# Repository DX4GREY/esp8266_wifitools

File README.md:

# WiFi Tools (esp8266)

Scan for WiFi devices, block selected connections, Start EvilTwin with custom html, create dozens of networks and confuse WiFi scanners.

## Password

The password for `A F` is `Dx4White`

## About this Project

This firmware allows you to easily perform a variety of actions to test 802.11 networks using an [ESP8266](https://www.espressif.com/en/products/socs/esp8266). It's also a great project for learning about WiFi, microcontrollers, Arduino, hacking and electronics/programming in general.  

The deauthentication attack is the main feature, which can be used to disconnect devices from their WiFi network.  
Although this denial-of-service attack is nothing new, a lot of devices are still vulnerable to it. Luckily this is slowly changing with more WiFi 6 enabled devices being used. But a lot of outdated WiFi devices remain in place, for example in cheap IoT hardware.
With an ESP8266 Deauther, you can easily test this attack on your 2.4GHz WiFi network/devices and see whether it's successful or not. And if it is, you know you should upgrade your network.

## Disclaimer

This project is a proof of concept for testing and educational purposes.  
Neither the ESP8266, nor its SDK was meant or built for such purposes. **Bugs can occur!**  

**Use it only against your own networks and devices!**  
Please check the legal regulations in your country before using it.  
We don't take any responsibility for what you do with this program.

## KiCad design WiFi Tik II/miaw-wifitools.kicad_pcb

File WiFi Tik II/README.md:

# WiFiTik Prototype
This project used base firmware [WiFi Tools](https://github.com/dx4grey/esp8266_wifitools)

## Component quantity

| Designator     | Quantity | Value                             | Pack                                | MPN                                | Mount Type |
| -------------- | -------- | --------------------------------- | ----------------------------------- | ---------------------------------- | ---------- |
| 1              | 1        | OLED                              |                                     |                                    | THT        |
| D1 MINI        | 1        | Wemos-D1-mini                     | wemos-d1-mini-connectors-only       |                                    | THT        |
| A, B, DOWN, UP | 4        | SW_PUSH_6mm                       | SW_PUSH_6mm                         |                                    | THT        |
| Hole, Hole, Hole, Hole | 4 | MountingHole_2.1mm              | MountingHole_2.1mm                  |                                    | THT        |
| LED            | 1        | LED_Cree-XQ_HandSoldering         | LED_Cree-XQ_HandSoldering           |                                    | SMT        |
| R1, R2         | 2        | Resistor                          | Resistor                            |                                    | THT        |
| RX, TX         | 2        | Pin_D0.9mm_L10.0mm_W2.4mm_FlatFork | Pin_D0.9mm_L10.0mm_W2.4mm_FlatFork |                                    | THT        |
| VIN            | 1        | Power 5V                           | Power 5V                            |                                    | SMT        |

## PCB Previews

<details>
  <summary>Front View</summary>

</details>

<details>
  <summary>Back View</summary>

</details>

## About this Project

This firmware allows you to easily perform a variety of actions to test 802.11 networks using an [ESP8266](https://www.espressif.com/en/products/socs/esp8266). It's also a great project for learning about WiFi, microcontrollers, Arduino, hacking and electronics/programming in general.  

The deauthentication attack is the main feature, which can be used to disconnect devices from their WiFi network.  
Although this denial-of-service attack is nothing new, a lot of devices are still vulnerable to it. Luckily this is slowly changing with more WiFi 6 enabled devices being used. But a lot of outdated WiFi devices remain in place, for example in cheap IoT hardware.
With an ESP8266 Deauther, you can easily test this attack on your 2.4GHz WiFi network/devices and see whether it's successful or not. And if it is, you know you should upgrade your network.

## Disclaimer

This project is a proof of concept for testing and educational purposes.  
Neither the ESP8266, nor its SDK was meant or built for such purposes. **Bugs can occur!**  

**Use it only against your own networks and devices!**  
Please check the legal regulations in your country before using it.  
We don't take any responsibility for what you do with this program.

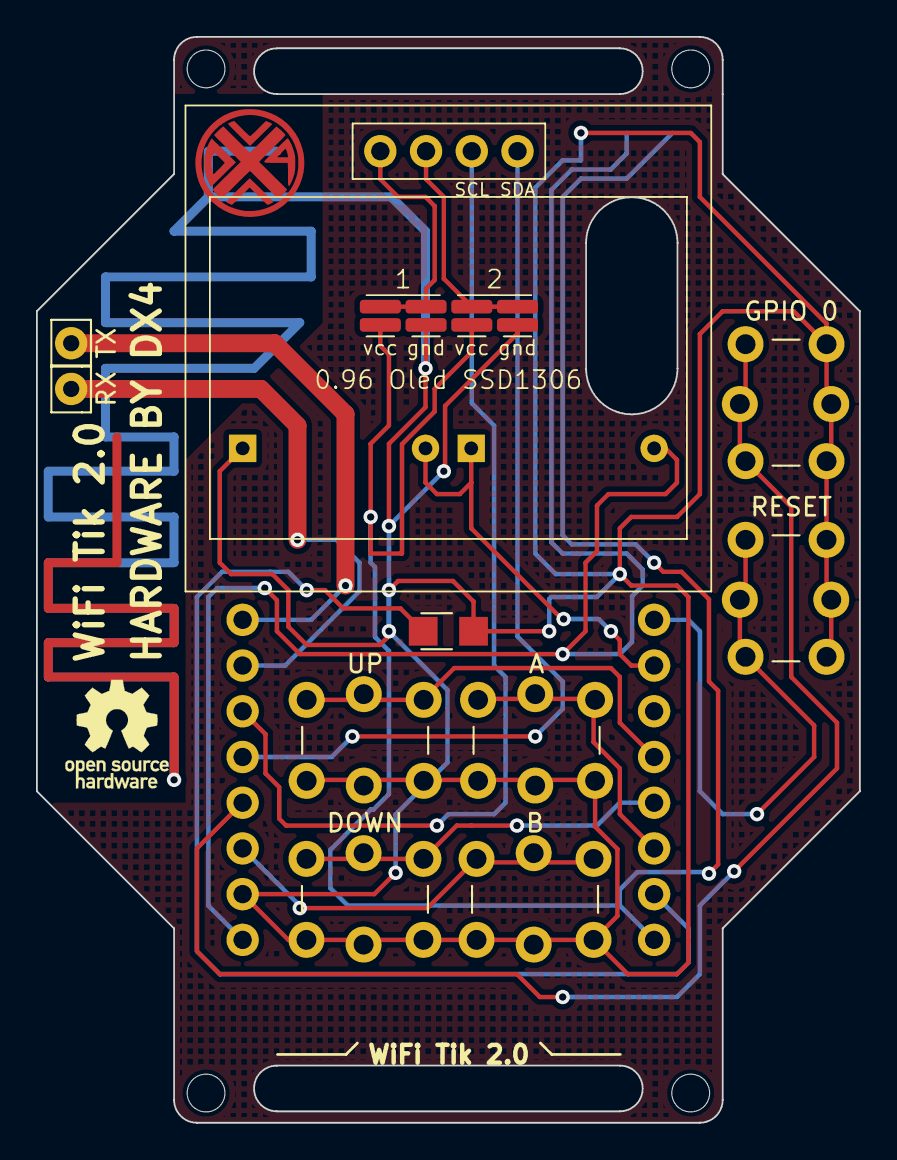
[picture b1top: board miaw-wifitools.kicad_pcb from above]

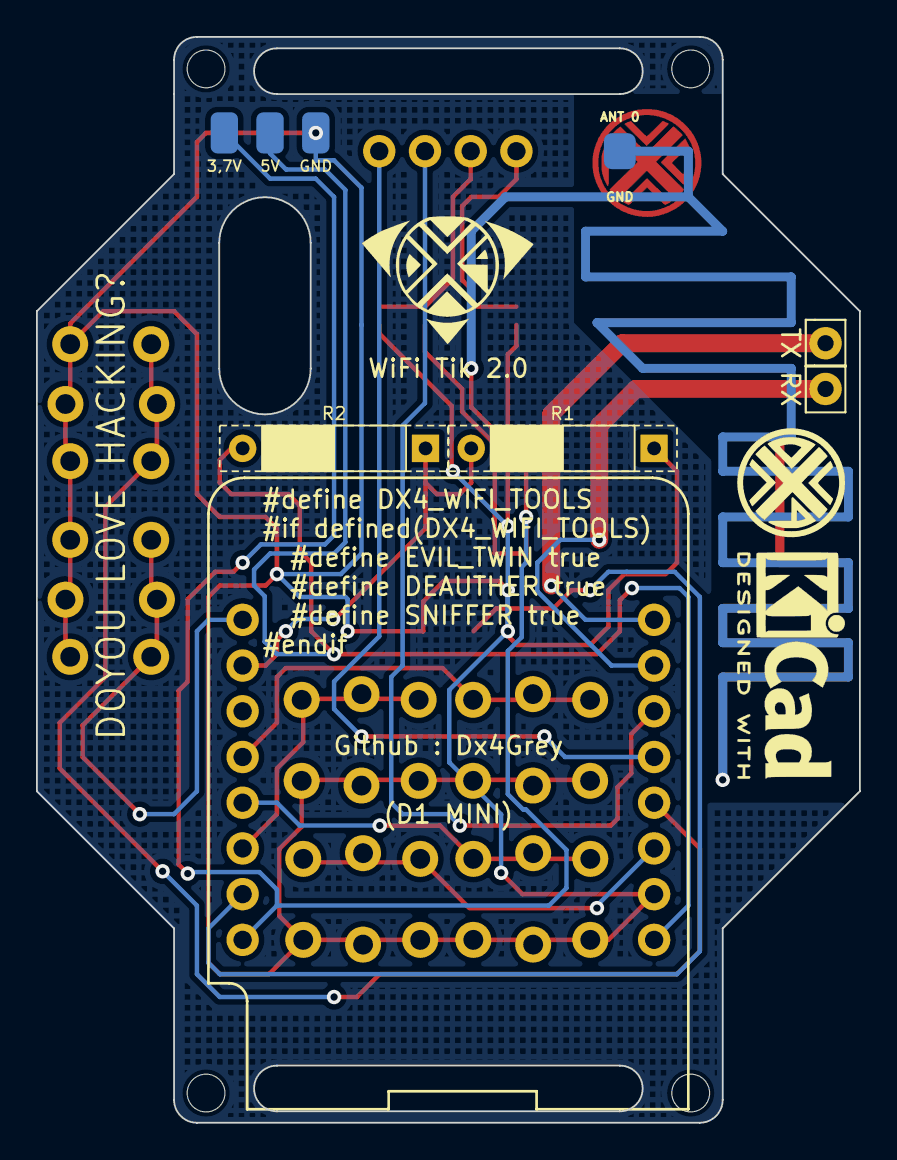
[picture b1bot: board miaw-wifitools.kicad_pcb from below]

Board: 2 copper layers, 45.7 x 60.3 mm, 20 parts (7 on the bottom side), 17 nets.

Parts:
0.96 Oled SSD1306: oled
(D1 MINI): Wemos-D1-mini; wemos-d1-mini-connectors-only
A: SW_PUSH_6mm
ANT 0: SolderWirePad_1x01_SMD_1x2mm
B: SW_PUSH_6mm
Battery: Power 5V
DOWN: SW_PUSH_6mm
GPIO 0: SW_PUSH_6mm
HOLE: MountingHole_2.1mm
HOLE#2, HOLE#3, HOLE#4: MountingHole_2.1mm
LED: LED_Cree-XQ_HandSoldering
R1, R2: Resistor
RESET: SW_PUSH_6mm
RX: Pin_D0.9mm_L10.0mm_W2.4mm_FlatFork
TX: Pin_D0.9mm_L10.0mm_W2.4mm_FlatFork
UP: SW_PUSH_6mm
display socket: OLED_CONNECTORS

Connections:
/1: 0.96 Oled SSD1306.1, display socket.1
/2: 0.96 Oled SSD1306.2, display socket.2
/5V5: (D1 MINI).9, Battery.1, R2.1
/A: (D1 MINI).6, A.1
/B: (D1 MINI).11, B.1
/BATLEVEL: (D1 MINI).2, R1.1, R2.2
/DOWN: (D1 MINI).5, DOWN.1
/GND: (D1 MINI).10, A.2, ANT 0.1, B.2, Battery.2, DOWN.2, GPIO 0.2, LED.2, R1.2, RESET.2, UP.2, display socket.2
/GPIO0: (D1 MINI).12, GPIO 0.1
/LED: (D1 MINI).7, LED.1
/RESET: (D1 MINI).1, RESET.1
/RX: (D1 MINI).15, RX.1
/SCL: 0.96 Oled SSD1306.3, (D1 MINI).14
/SDA: 0.96 Oled SSD1306.4, (D1 MINI).13
/TX: (D1 MINI).16, TX.1
/UP: (D1 MINI).4, UP.1
/VCC: (D1 MINI).8, Battery.1, display socket.2

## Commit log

2023-12-07 Big update
2023-12-09 Display
2023-12-15 Bigger Update For Display
2023-12-28 Update Evil Twin
2024-01-21 Update Device Com
2024-01-25 Update PCBs
2024-01-29 Update README and preview PCBs
2024-01-30 Update Attack Method (Web Server)
2024-02-14 Update Repeater
